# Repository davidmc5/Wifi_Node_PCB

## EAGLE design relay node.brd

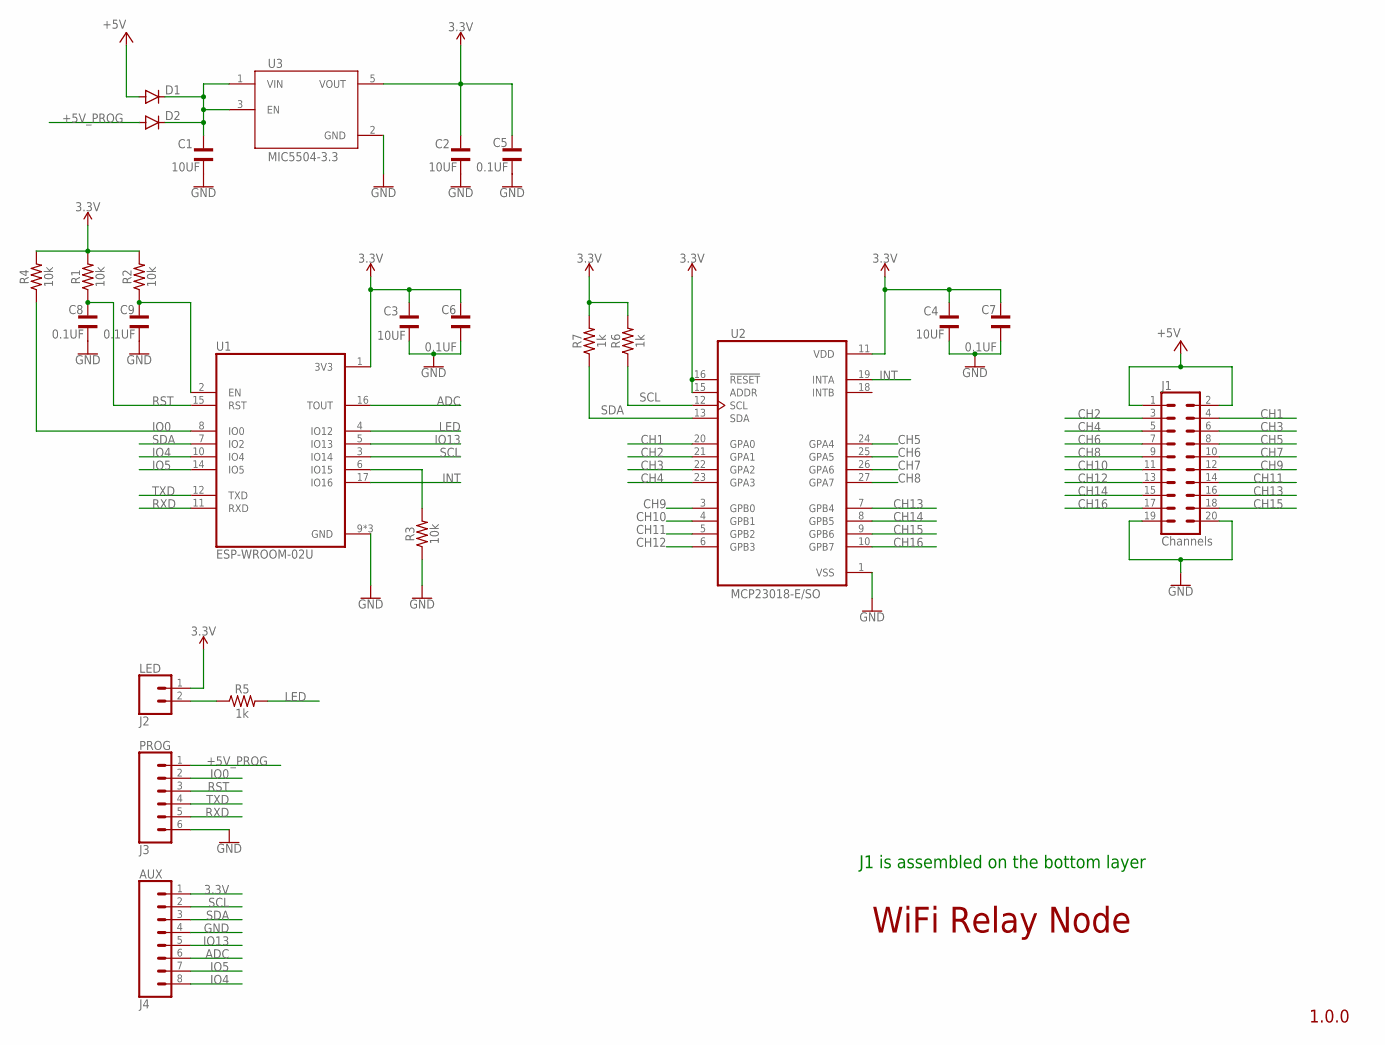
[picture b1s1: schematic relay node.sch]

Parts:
C1, C2, C3, C4: 10UF; CAPC2012X135N
C5, C6, C7, C8, C9: 0.1UF; CAPC1608X90
D1, D2: MBR0520LT; SOD123
J1: Channels; 2X10_NOSILK
J2: LED; 1X02
J3: PROG; 1X06
J4: AUX; 1X08
R1, R2, R3, R4: 10k; 0603
R5, R6, R7: 1k; 0603
U1: ESP-WROOM-02U; MODULE_ESP-WROOM-02U
U2: MCP23018-E/SO; SOIC127P1030X265-28N
U3: MIC5504-3.3; SOT95P280X145-5N

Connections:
3.3V: C2.1, C3.1, C4.1, C5.1, C6.1, C7.1, J2.1, J4.1, R1.2, R2.2, R4.2, R6.2, R7.2, U1.1 (3V3), U2.11 (VDD), U2.15 (ADDR), U2.16 (!RESET), U3.5 (VOUT)
+5V: D1.A, J1.1, J1.2
+5V_PROG: D2.A, J3.1
ADC: J4.6, U1.16 (TOUT)
CH1: J1.4, U2.20 (GPA0)
CH2: J1.3, U2.21 (GPA1)
CH3: J1.6, U2.22 (GPA2)
CH4: J1.5, U2.23 (GPA3)
CH5: J1.8, U2.24 (GPA4)
CH6: J1.7, U2.25 (GPA5)
CH7: J1.10, U2.26 (GPA6)
CH8: J1.9, U2.27 (GPA7)
CH9: J1.12, U2.3 (GPB0)
CH10: J1.11, U2.4 (GPB1)
CH11: J1.14, U2.5 (GPB2)
CH12: J1.13, U2.6 (GPB3)
CH13: J1.16, U2.7 (GPB4)
CH14: J1.15, U2.8 (GPB5)
CH15: J1.18, U2.9 (GPB6)
CH16: J1.17, U2.10 (GPB7)
GND: C1.2, C2.2, C3.2, C4.2, C5.2, C6.2, C7.2, C8.2, C9.2, J1.19, J1.20, J3.6, J4.4, R3.1, U1.9 (GND), U1.13 (GND), U1.18 (GND), U2.1 (VSS), U3.2 (GND)
INT: U1.17 (IO16), U2.19 (INTA)
IO0: J3.2, R4.1, U1.8 (IO0)
IO4: J4.8, U1.10 (IO4)
IO5: J4.7, U1.14 (IO5)
IO13: J4.5, U1.5 (IO13)
LED: R5.2, U1.4 (IO12)
unnamed: C1.1, D1.C, D2.C, U3.1 (VIN), U3.3 (EN)
unnamed: R3.2, U1.6 (IO15)
unnamed: C9.1, R2.1, U1.2 (EN)
unnamed: J2.2, R5.1
RST: C8.1, J3.3, R1.1, U1.15 (RST)
RXD: J3.5, U1.11 (RXD)
SCL: J4.2, R6.1, U1.3 (IO14), U2.12 (SCL)
SDA: J4.3, R7.1, U1.7 (IO2), U2.13 (SDA)
TXD: J3.4, U1.12 (TXD)

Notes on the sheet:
1.0.0
WiFi Relay Node
J1 is assembled on the bottom layer

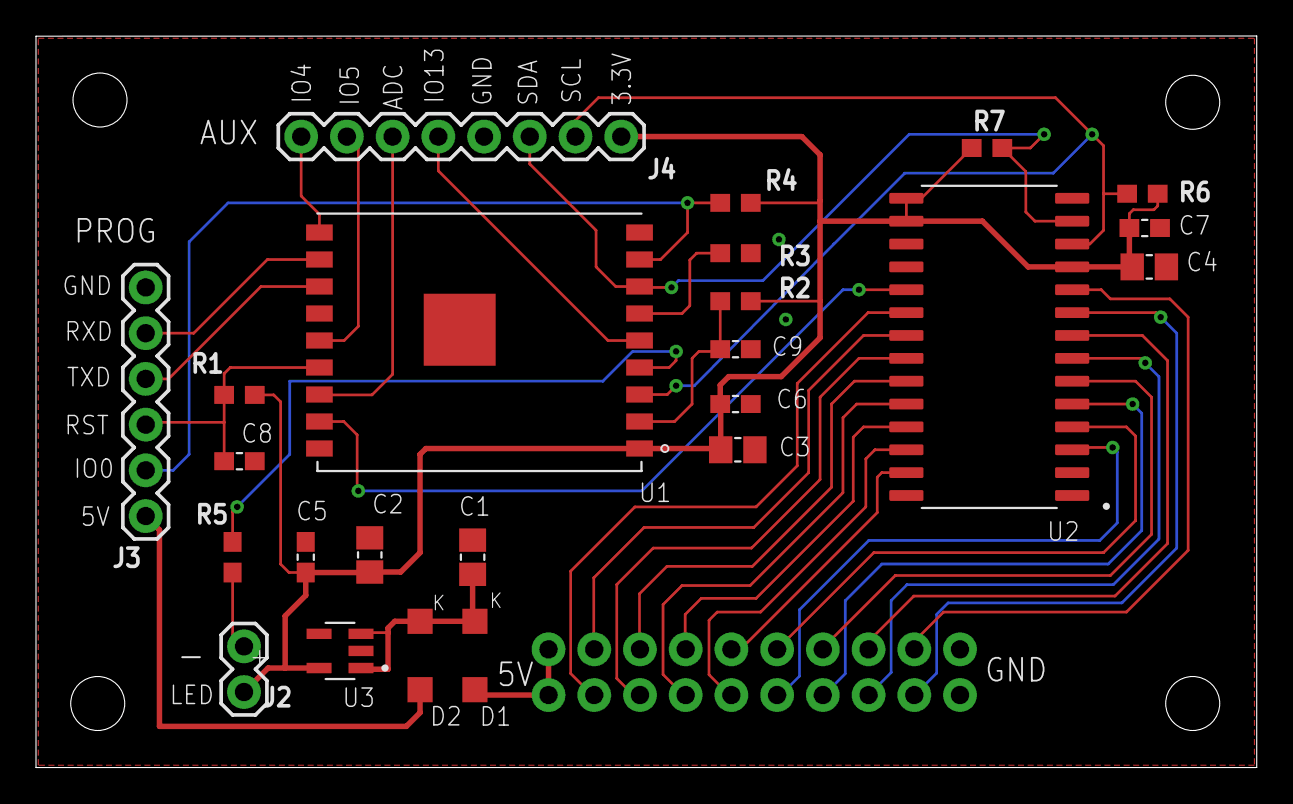
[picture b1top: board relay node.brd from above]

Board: 2 copper layers, 67.8 x 40.6 mm, 25 parts (1 on the bottom side), 36 nets.

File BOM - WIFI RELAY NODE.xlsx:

Qty | Value | Device | Package | Parts | Description | DIGI-KEY_PART_NUMBER | DIGI-KEY_PURCHASE_URL | MF | MPN | PRICE | Extended price | Comments
0 | 20V 0.5A | Diode MBR0520 | SOD123 | D1, D2 | Diode Schottky 20V 500mA | MBR0520LT3GOSCT-ND | https://www.digikey.com/product-detail/en/on-semiconductor/M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 | ON Semiconductor | MBR0520LT3G | 0.34 | 0
2 | 20V 0.5A | Diode MBR0520 | SOD123 | D1, D2 | Diode Schottky 20V 500mA | MBR0520LT1GOSCT-ND | https://www.digikey.com/product-detail/en/on-semiconductor/M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 | ON Semiconductor | MBR0520LT3G | 0.04 | 0.08 | For JLCPCB - Digikey had 0 stock
5 | 0.1uF | 0.1UF 25V-20% | 0603 | C5, C6, C7, C8, C9 | 0.1µF ceramic capacitors | 399-1100-1-ND | https://www.digikey.com/product-detail/en/kemet/C0603C104Z3V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 | KEMET | C0603C104Z3VACTU | 0.1 | 0.5
4 | 10uF | 10UF-25V-20% | 0805 | C1, C2, C3, C4 | 10.0µF ceramic capacitors | 490-10503-1-ND | https://www.digikey.com/product-detail/en/murata-electronics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 | Murata Electronics | GRM21BC81E106ME51L | 0.37 | 1.48
4 | 10k | 10KOHM-0603-1/10W-5% | 0603 | R1, R2, R3, R4 | 10k resistor | 311-10KGRCT-ND | https://www.digikey.com/product-detail/en/yageo/RC0603JR-071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 | Yageo | RC0603JR-0710KL | 0.1 | 0.4
3 | 1k | 1KOHM-0603-1/10W-5% | 603 | R5, R6, R7 | 1k resistor | 311-1.0KGRCT-ND | https://www.digikey.com/product-detail/en/yageo/RC0603JR-071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 | Yageo | RC0603JR-071KL | 0.1 | 0.30000000000000004
0 | 8-pin male header | CONN_1X08 | 1x08 | J4 | Header-pin |  |  |  |  |  | 0
1 | ESP-WROOM-02U | ESP-WROOM-02U | 18-SMD Module | U1 | WiFi module | 1904-1022-1-ND | https://www.digikey.com/product-detail/en/espressif-systems/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 | Espressif Systems | ESP-WROOM-02U | 3.2 | 3.2
1 | 2-Pin male header | CONN_1X02 | 1X02 (Pitch 2.54mm) | J2 | 2-Pin male header | 952-2262-ND | https://www.digikey.com/product-detail/en/harwin-inc/M20-999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 | Harwin | M20-9990246 | 0.11 | 0.11
1 | 6-Pin male header | CONN_1X06 | 1X06 (Pitch 2.54mm) | J3 | 6-Pin male header | 609-3263-ND | https://www.digikey.com/product-detail/en/amphenol-icc-fci/6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 | Amphenol | 68000-406HLF | 0.27 | 0.27
1 | 20-pin Female header | CONN_2X10 | 2X10 (Pitch 2.54mm) | J1 | 20-pin Female header | S7078-ND | https://www.digikey.com/product-detail/en/sullins-connector-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 | Sullins | PPTC102LFBN-RC | 1.3 | 1.3
 |  |  |  |  |  |  |  |  |  |  | 0
0 | TLV75533 | Voltage regulator 3.3 V - 500 mA | SOT-23-5 | U3 | Linear Voltage Regulator | 296-50411-1-ND | https://www.digikey.com/product-detail/en/texas-instruments/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 | Texas Instruments | TLV75533PDBVR | 0.39 | 0
1 | MIC5504-3.3 | Voltage regulator 3.3 V - 300 mA | SOT-23-5 | U3 | Linear Voltage Regulator | 576-4764-1-ND | https://www.digikey.com/product-detail/en/microchip-technolo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 | Microchip Technology | MIC5504-3.3YM5-TR | 0.11 | 0.11 | For JLCPCB
 |  |  |  |  |  |  |  |  |  |  | 0
0 | MCP23018 | I/O expander 16bit | 24-SSOP | U2 | I/O expander 16bit | MCP23018-E/SS-ND | https://www.digikey.com/product-detail/en/microchip-technolo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 | Microchip Technology | MCP23018-E/SS | 1.66 | 0
1 | MCP23018 | I/O expander 16bit | 28-SOIC | U2 | I/O expander 16bit | MCP23018-E/SO-ND | https://www.digikey.com/product-detail/en/microchip-technolo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 | Microchip Technology | MCP23018-E/SO | 1.51 | 1.51 | Larger pitch to make it easier to solder by hand
0 | MCP23018 | MCP23018T-E/SO | 28-SOIC | U2 | I/O expander 16bit | MCP23018T-E/SOCT-ND | https://www.digikey.com/product-detail/en/microchip-technolo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 | Microchip Technology | MCP23018T-E/SO | 1.51 | 0
0 | MCP23017 | MCP23017 | 28-SOIC | U2 | 16 IO expander | MCP23017T-E/SOCT-ND | https://www.digikey.com/product-detail/en/microchip-technolo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 | MICROCHIP | MCP23017T-E/SO | 1.2 | 0

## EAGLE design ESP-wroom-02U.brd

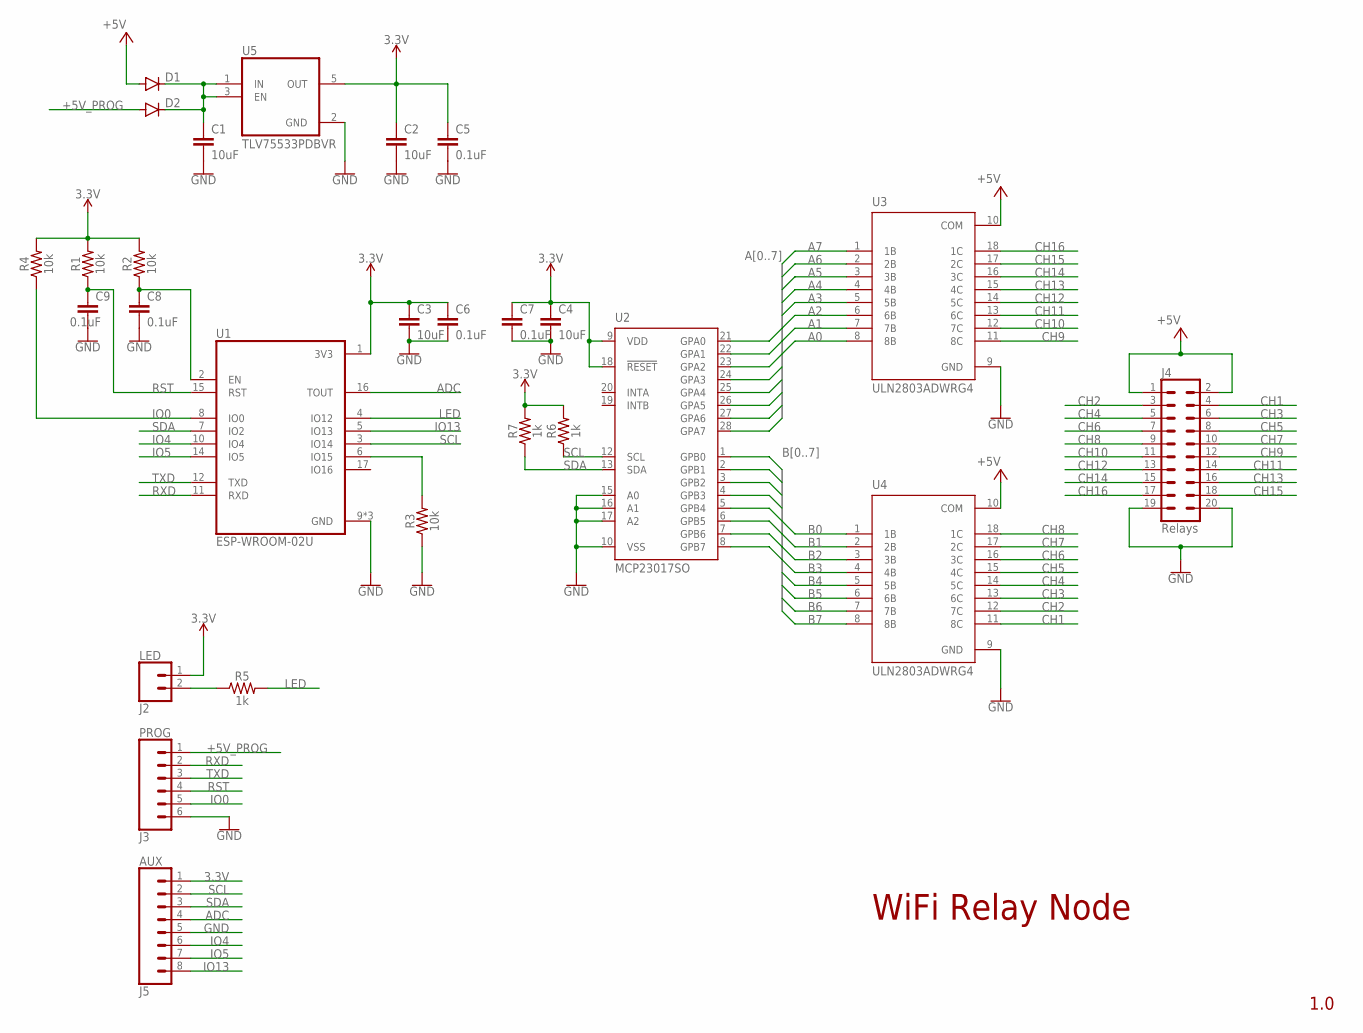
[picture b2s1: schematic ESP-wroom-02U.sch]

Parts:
C1, C2, C3, C4: 10uF; 0805
C5, C6, C7, C8, C9: 0.1uF; 0603
D1, D2: MBR0520LT; SOD123
J2: LED; 1X02
J3: PROG; 1X06
J4: Relays; 2X10
J5: AUX; 1X08
R1, R2, R3, R4: 10k; 0603
R5, R6, R7: 1k; 0603
U1: ESP-WROOM-02U; MODULE_ESP-WROOM-02U
U2: MCP23017SO; SO28W
U3, U4: ULN2803ADWRG4; SOIC127P1030X265-18N
U5: TLV75533PDBVR; SOT95P280X145-5N

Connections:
3.3V: C2.1, C3.1, C4.1, C5.1, C6.1, C7.1, J2.1, J5.1, R1.2, R2.2, R4.2, R6.2, R7.2, U1.1 (3V3), U2.9 (VDD), U2.18 (!RESET), U5.5 (OUT)
+5V: D1.A, J4.1, J4.2, U3.10 (COM), U4.10 (COM)
+5V_PROG: D2.A, J3.1
A0: U2.21 (GPA0), U3.8 (8B)
A1: U2.22 (GPA1), U3.7 (7B)
A2: U2.23 (GPA2), U3.6 (6B)
A3: U2.24 (GPA3), U3.5 (5B)
A4: U2.25 (GPA4), U3.4 (4B)
A5: U2.26 (GPA5), U3.3 (3B)
A6: U2.27 (GPA6), U3.2 (2B)
A7: U2.28 (GPA7), U3.1 (1B)
ADC: J5.4, U1.16 (TOUT)
B0: U2.1 (GPB0), U4.1 (1B)
B1: U2.2 (GPB1), U4.2 (2B)
B2: U2.3 (GPB2), U4.3 (3B)
B3: U2.4 (GPB3), U4.4 (4B)
B4: U2.5 (GPB4), U4.5 (5B)
B5: U2.6 (GPB5), U4.6 (6B)
B6: U2.7 (GPB6), U4.7 (7B)
B7: U2.8 (GPB7), U4.8 (8B)
CH1: J4.4, U4.11 (8C)
CH2: J4.3, U4.12 (7C)
CH3: J4.6, U4.13 (6C)
CH4: J4.5, U4.14 (5C)
CH5: J4.8, U4.15 (4C)
CH6: J4.7, U4.16 (3C)
CH7: J4.10, U4.17 (2C)
CH8: J4.9, U4.18 (1C)
CH9: J4.12, U3.11 (8C)
CH10: J4.11, U3.12 (7C)
CH11: J4.14, U3.13 (6C)
CH12: J4.13, U3.14 (5C)
CH13: J4.16, U3.15 (4C)
CH14: J4.15, U3.16 (3C)
CH15: J4.18, U3.17 (2C)
CH16: J4.17, U3.18 (1C)
GND: C1.2, C2.2, C3.2, C4.2, C5.2, C6.2, C7.2, C8.2, C9.2, J3.6, J4.19, J4.20, J5.5, R3.1, U1.9 (GND), U1.13 (GND), U1.18 (GND), U2.10 (VSS), U2.15 (A0), U2.16 (A1), U2.17 (A2), U3.9 (GND), U4.9 (GND), U5.2 (GND)
IO0: J3.5, R4.1, U1.8 (IO0)
IO4: J5.6, U1.10 (IO4)
IO5: J5.7, U1.14 (IO5)
IO13: J5.8, U1.5 (IO13)
LED: R5.2, U1.4 (IO12)
unnamed: C1.1, D1.C, D2.C, U5.1 (IN), U5.3 (EN)
unnamed: R3.2, U1.6 (IO15)
unnamed: C8.1, R2.1, U1.2 (EN)
unnamed: J2.2, R5.1
RST: C9.1, J3.4, R1.1, U1.15 (RST)
RXD: J3.2, U1.11 (RXD)
SCL: J5.2, R6.1, U1.3 (IO14), U2.12 (SCL)
SDA: J5.3, R7.1, U1.7 (IO2), U2.13 (SDA)
TXD: J3.3, U1.12 (TXD)

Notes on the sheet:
1.0
WiFi Relay Node

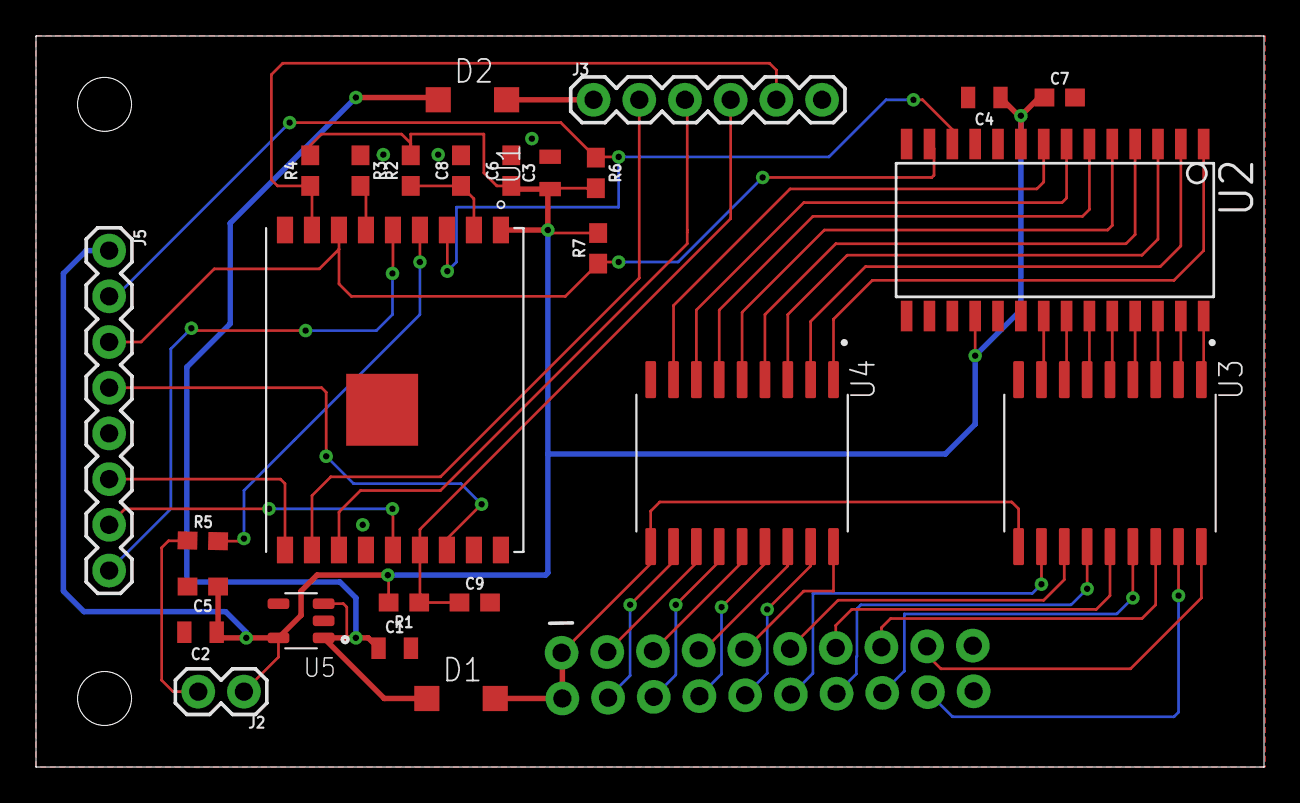
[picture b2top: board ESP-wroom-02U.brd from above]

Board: 2 copper layers, 68.2 x 40.6 mm, 27 parts (1 on the bottom side), 51 nets.

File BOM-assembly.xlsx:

Qty | Value | Device | Package | Parts | Description | DIGI-KEY_PART_NUMBER | DIGI-KEY_PURCHASE_URL | MF | MPN | PRICE
2 | Diode Schottky 20V 0.5A | Diode MBR0520 | SOD123 | D1, D2 | Diode Schottky 20V 500mA | MBR0520LT1GOSCT-ND | https://www.digikey.com/product-detail/en/on-semiconductor/M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 | ON Semiconductor | MBR0520LT3G | 0.04
5 | 0.1uF | 0.1UF 25V-20% | 0603 | C5, C6, C7, C8, C9 | 0.1µF ceramic capacitors | 399-1100-1-ND | https://www.digikey.com/product-detail/en/kemet/C0603C104Z3V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 | KEMET | C0603C104Z3VACTU | 0.1
4 | 10uF | 10UF-25V-20% | 0805 | C1, C2, C3, C4 | 10.0µF ceramic capacitors | 490-10503-1-ND | https://www.digikey.com/product-detail/en/murata-electronics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 | Murata Electronics | GRM21BC81E106ME51L | 0.37
4 | 10k | 10KOHM-0603-1/10W-5% | 0603 | R1, R2, R3, R4 | 10k resistor | 311-10KGRCT-ND | https://www.digikey.com/product-detail/en/yageo/RC0603JR-071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 | Yageo | RC0603JR-0710KL | 0.1
3 | 1k | 1KOHM-0603-1/10W-5% | 603 | R5, R6, R7 | 1k resistor | 311-1.0KGRCT-ND | https://www.digikey.com/product-detail/en/yageo/RC0603JR-071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 | Yageo | RC0603JR-071KL | 0.1
1 | ESP-WROOM-02U | ESP-WROOM-02U | 18-SMD Module | U1 | WiFi module | 1904-1022-1-ND | https://www.digikey.com/product-detail/en/espressif-systems/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 | Espressif Systems | ESP-WROOM-02U | 3.2
1 | MIC5504-3.3 | Voltage regulator 3.3 V - 300 mA | SOT-23-5 | U3 | Linear Voltage Regulator | 576-4764-1-ND | https://www.digikey.com/product-detail/en/microchip-technolo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 | Microchip Technology | MIC5504-3.3YM5-TR | 0.11
1 | MCP23018 | I/O expander 16bit | 28-SOIC | U2 | I/O expander 16bit | MCP23018-E/SO-ND | https://www.digikey.com/product-detail/en/microchip-technolo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 | Microchip Technology | MCP23018-E/SO | 1.51
1 | 2-Pin male header | CONN_1X02 | 1X02 (Pitch 2.54mm) | J2 | 2-Pin male header | 952-2262-ND | https://www.digikey.com/product-detail/en/harwin-inc/M20-999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 | Harwin | M20-9990246 | 0.11
1 | 6-Pin male header | CONN_1X06 | 1X06 (Pitch 2.54mm) | J3 | 6-Pin male header | 609-3263-ND | https://www.digikey.com/product-detail/en/amphenol-icc-fci/6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 | Amphenol | 68000-406HLF | 0.27
1 | 20-pin Female header | CONN_2X10 | 2X10 (Pitch 2.54mm) | J1 | 20-pin Female header | S7078-ND | https://www.digikey.com/product-detail/en/sullins-connector-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 | Sullins | PPTC102LFBN-RC | 1.3

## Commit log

2020-06-16 Initial commit Using MCP23017 and 2 x ULN2803 NPN arrays
2020-06-16 Edited wifi IC footprint - Removed solder mask and solder paste (tcream layer) from esp-wroom IC -Updated BOM
2020-06-16 Minor changes
2020-06-20 Move J1 to bottom layer Add J1 to J3 connectors to BOM for quotes
2020-06-27 Replace I/O expander to MCP23018 28-SOIC Replace BOM part numbers to match JLCPB inventory
2020-06-28 Replace volt regulator
2020-06-28 Minor changes for production PCB ordered - v1.0.0

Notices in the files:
parts and their libraries:
SparkFun-PowerSymbols: Licensing: Creative Commons ShareAlike 4.0 International - https://creativecommons.org/licenses/by-sa/4.0
